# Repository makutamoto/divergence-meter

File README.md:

Divergence Meter
=====
PICの勉強のために作りました。
言語はMPASMです。

[実際に動いているところ（ブレッドボード上ですが）](https://twitter.com/makutamoto/status/1317350844782632962?s=20)

divergence_meter.X/
-----
MPLABのプロジェクトです。
PICのコードが入っています。

pcb/
-----
KICADのプロジェクトです。
基盤データが入っています。

scripts/
-----
ダイバージェンスメータに様々な情報を書き込むためのスクリプトを置いています。

### add.py
世界戦変動率を追加します。

### calibrate.py
現在時刻と同期します。

### clock.py
忘れた、不明。

### preview.py
世界戦変動率をプレビューします。

### remove.py
世界戦変動率を削除します。

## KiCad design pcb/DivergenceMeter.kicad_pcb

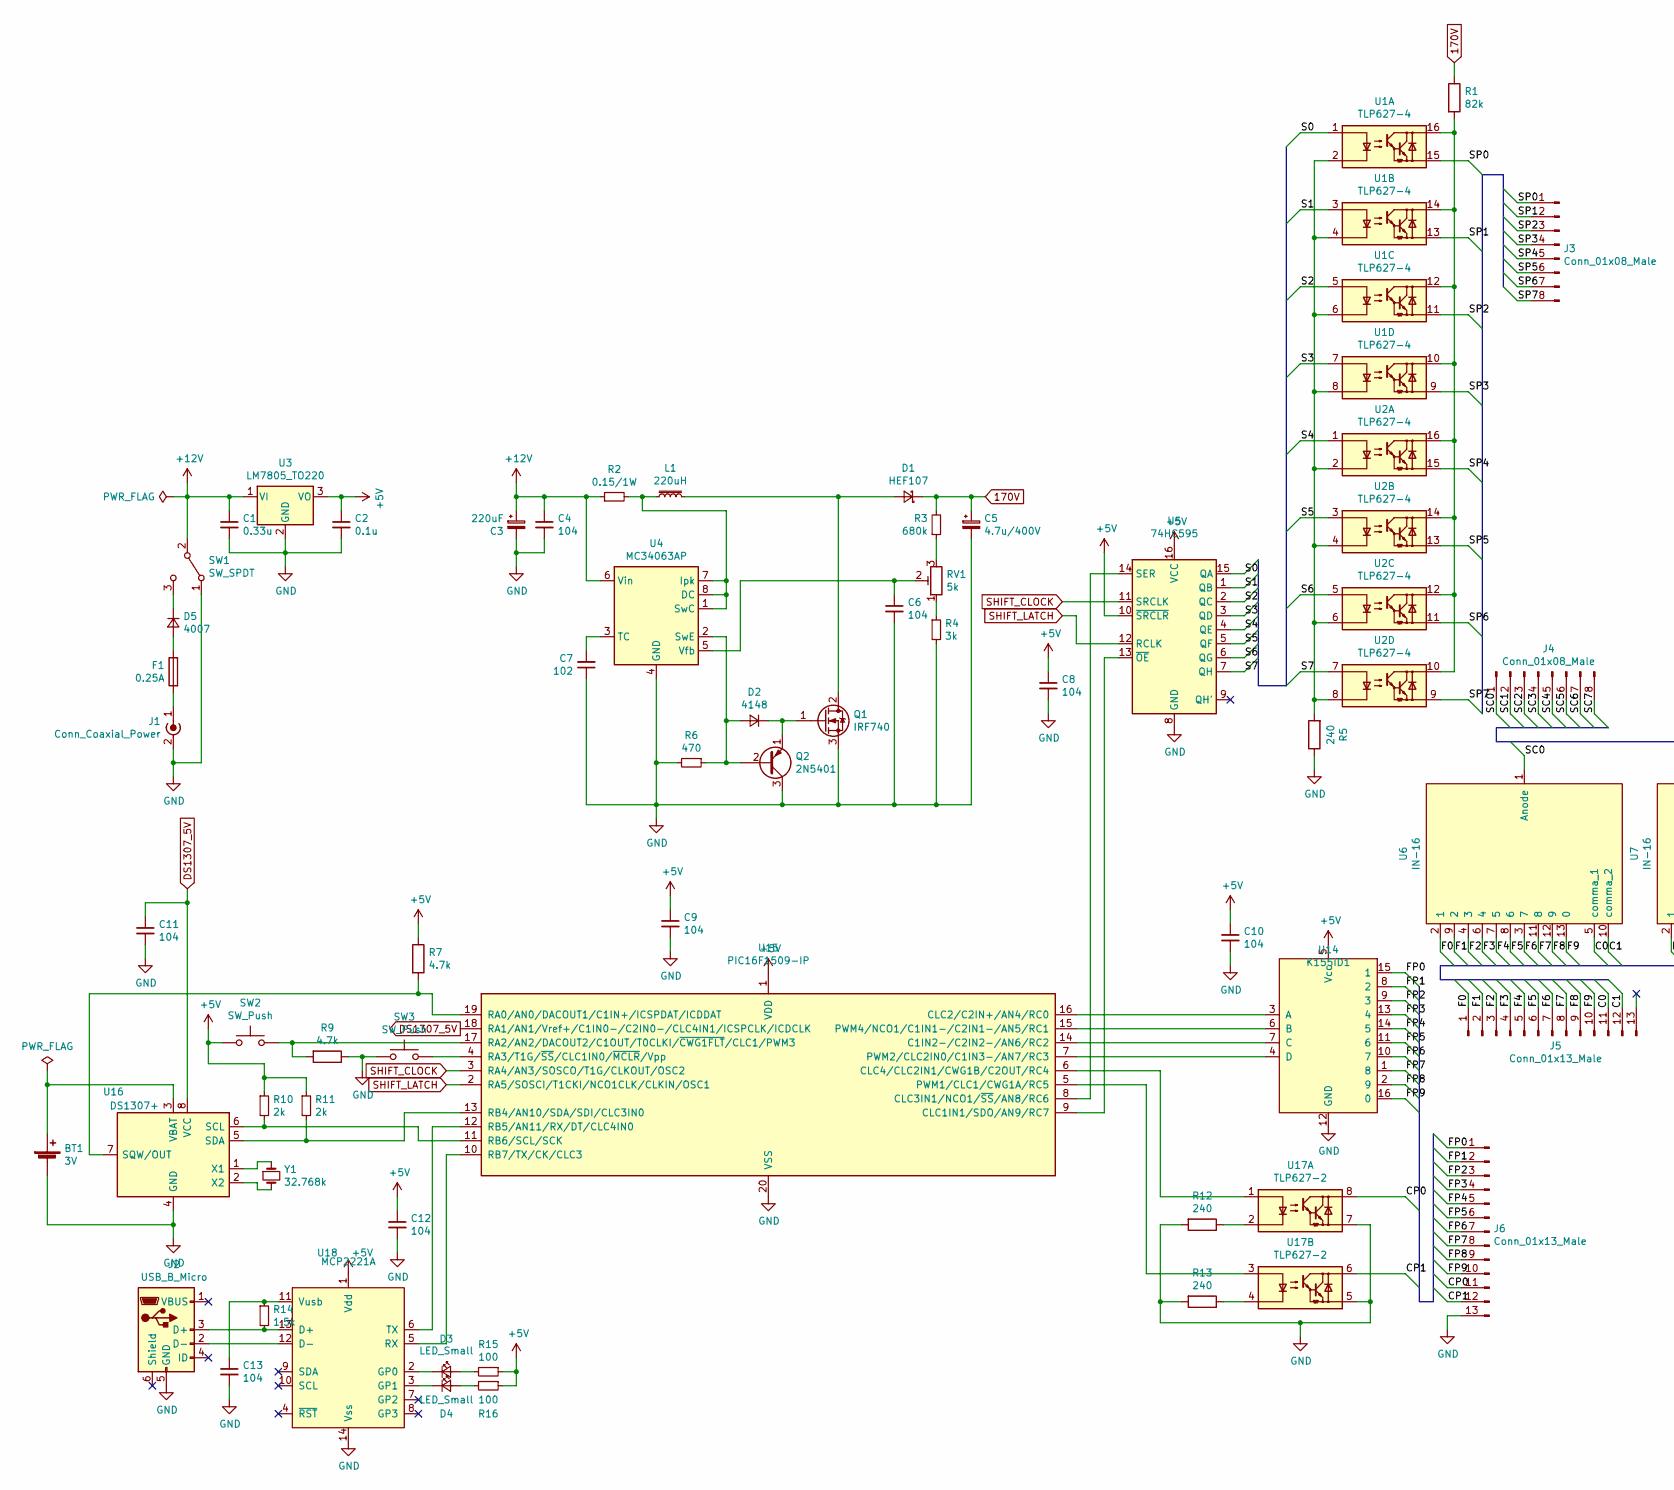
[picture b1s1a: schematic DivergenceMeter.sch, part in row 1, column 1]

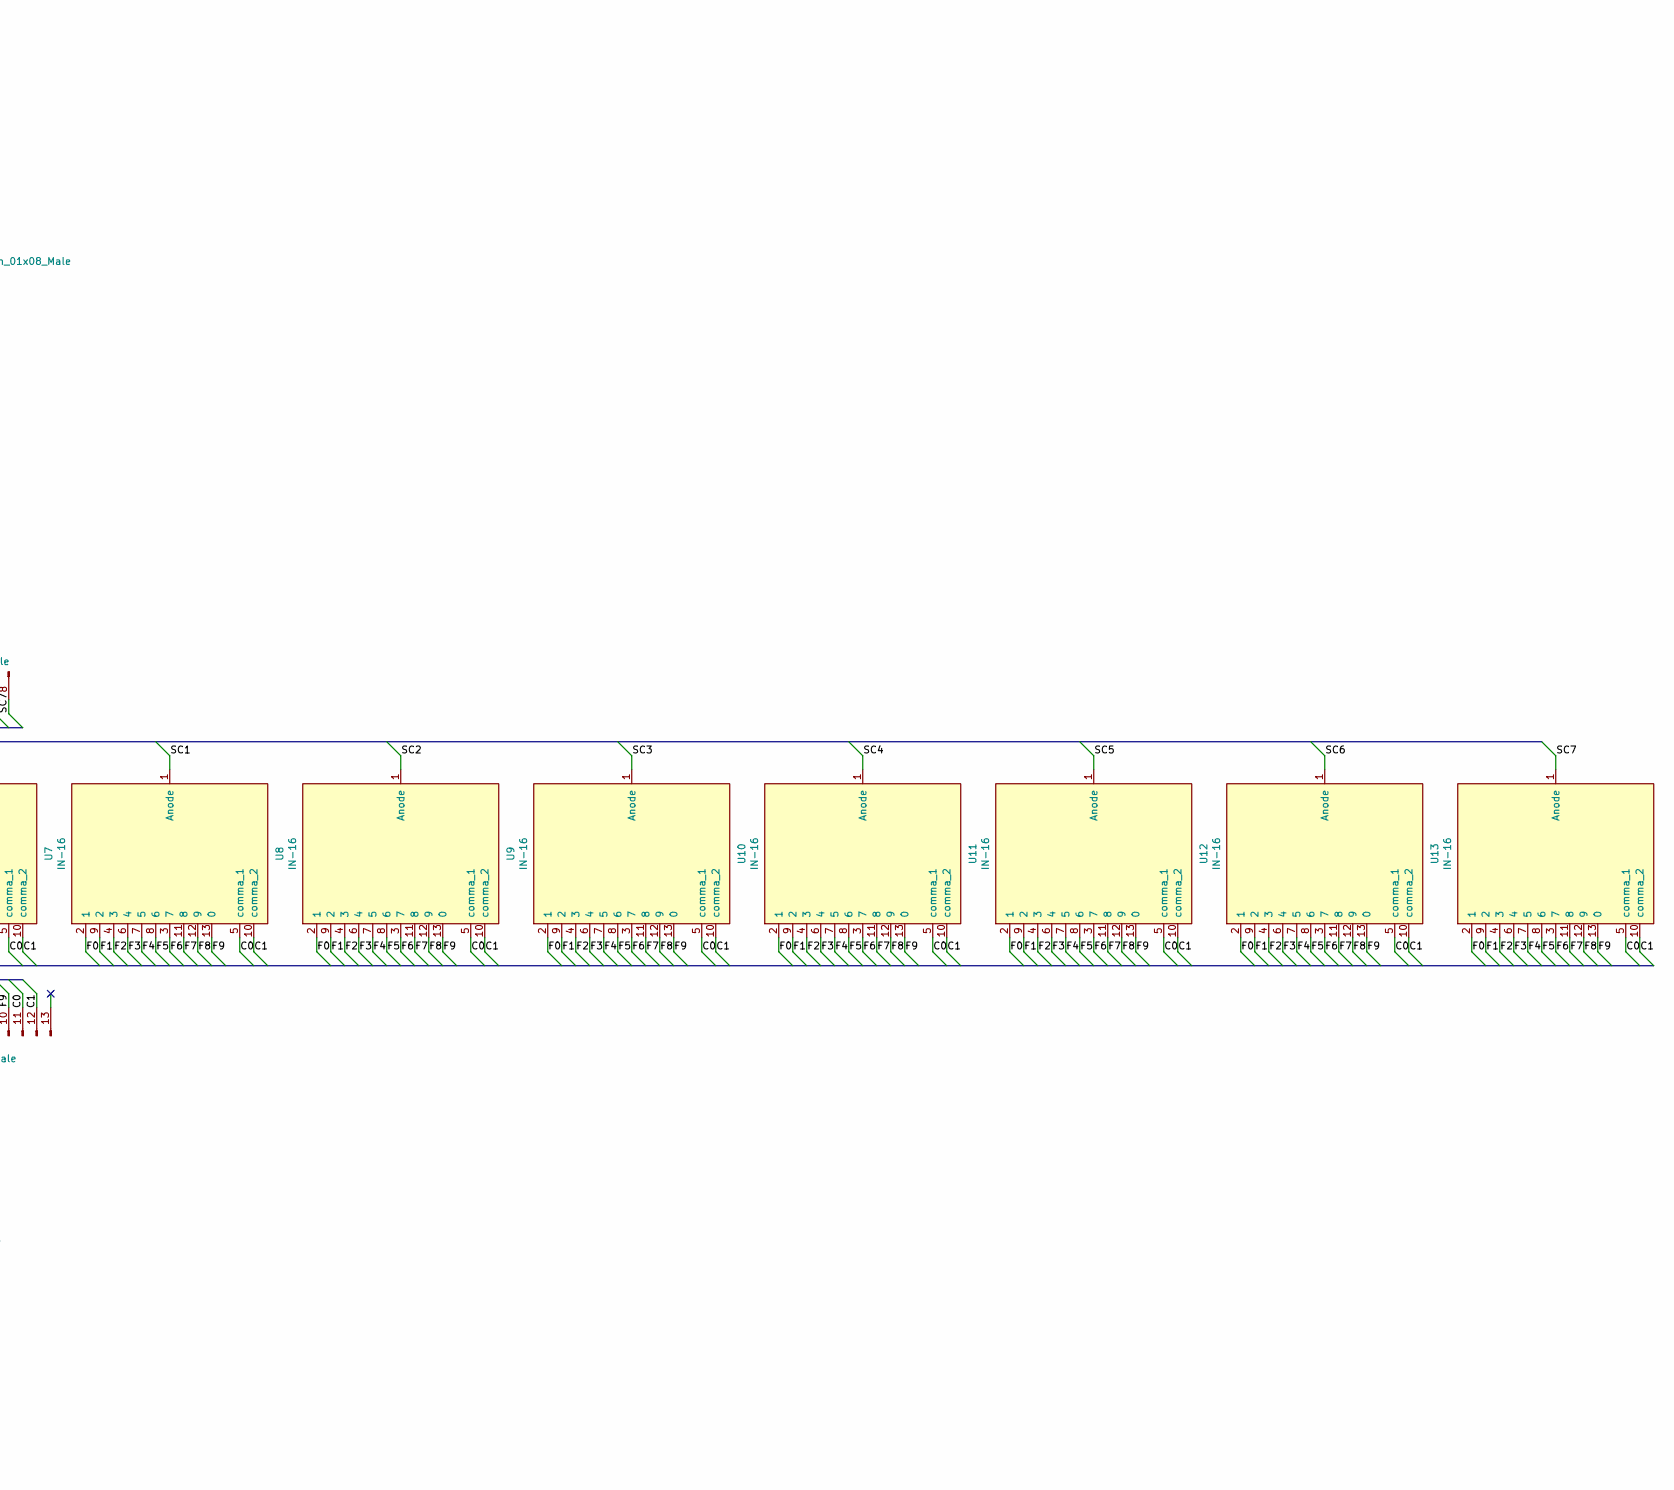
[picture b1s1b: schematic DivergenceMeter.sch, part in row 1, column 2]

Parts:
BT1: 3V; BatteryHolder_Keystone_103_1x20mm
C1: 0.33u; C_Radial_D10.0mm_H12.5mm_P5.00mm
C2: 0.1u; C_Radial_D10.0mm_H12.5mm_P5.00mm
C3: 220uF; CP_Radial_D10.0mm_P5.00mm
C4, C6, C8, C9, C10, C11, C12, C13: 104; C_Radial_D10.0mm_H12.5mm_P5.00mm
C5: 4.7u/400V; CP_Radial_D10.0mm_P5.00mm
C7: 102; C_Radial_D16.0mm_H25.0mm_P7.50mm
D1: HEF107; D_DO-41_SOD81_P10.16mm_Horizontal
D2: 4148; D_DO-35_SOD27_P7.62mm_Horizontal
D3, D4: LED_Small; LED_D3.0mm
D5: 4007; D_DO-41_SOD81_P10.16mm_Horizontal
F1: 0.25A; Fuseholder_Cylinder-5x20mm_Schurter_0031_8201_Horizontal_Op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
J1: Conn_Coaxial_Power; DC Jack
J2: USB_B_Micro; USB_Micro-B_Molex-105017-0001
J3, J4: Conn_01x08_Male; JST_XH_B08B-XH-A_1x08_P2.50mm_Vertical
J5, J6: Conn_01x13_Male; JST_XH_B13B-XH-A_1x13_P2.50mm_Vertical
L1: 220uH; L_Radial_D6.0mm_P4.00mm
Q1: IRF740; TO-220-3_Vertical
Q2: 2N5401; TO-92_Inline
R1: 82k; R_Axial_DIN0207_L6.3mm_D2.5mm_P10.16mm_Horizontal
R2: 0.15/1W; R_Axial_DIN0207_L6.3mm_D2.5mm_P10.16mm_Horizontal
R3: 680k; R_Axial_DIN0207_L6.3mm_D2.5mm_P10.16mm_Horizontal
R4: 3k; R_Axial_DIN0207_L6.3mm_D2.5mm_P10.16mm_Horizontal
R5, R12, R13: 240; R_Axial_DIN0207_L6.3mm_D2.5mm_P10.16mm_Horizontal
R6: 470; R_Axial_DIN0207_L6.3mm_D2.5mm_P10.16mm_Horizontal
R7, R9: 4.7k; R_Axial_DIN0207_L6.3mm_D2.5mm_P10.16mm_Horizontal
R10, R11: 2k; R_Axial_DIN0207_L6.3mm_D2.5mm_P10.16mm_Horizontal
R14: 1.5k; R_Axial_DIN0207_L6.3mm_D2.5mm_P10.16mm_Horizontal
R15, R16: 100; R_Axial_DIN0207_L6.3mm_D2.5mm_P10.16mm_Horizontal
RV1: 5k; Potentiometer_Bourns_3266P_Horizontal
SW1: SW_SPDT; Slide Switch
SW2, SW3: SW_Push; SW_PUSH_6mm_H5mm
U1, U2: TLP627-4; DIP-16_W7.62mm
U3: LM7805_TO220; TO-220-3_Vertical
U4: MC34063AP; DIP-8_W7.62mm
U5: 74HC595; DIP-16_W7.62mm
U6, U7, U8, U9, U10, U11, U12, U13: IN-16
U14: K155ID1; DIP-16_W7.62mm
U15: PIC16F1509-IP; DIP-20_W7.62mm_Socket
U16: DS1307+; DIP-8_W7.62mm
U17: TLP627-2; DIP-8_W7.62mm
U18: MCP2221A; DIP-14_W7.62mm
Y1: 32.768k; Crystal_DS26_D2.0mm_L6.0mm_Vertical

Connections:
170V: C5.1, D1.1 (K), R1.1, R3.2
+5V: C2.1, C8.1, C9.1, C10.1, C12.1, R7.1, R10.1, R11.1, R15.1, R16.1, SW2.1, U3.3 (VO), U5.10 (~SRCLR), U5.16 (VCC), U14.5 (Vcc), U15.1 (VDD), U18.1 (Vdd)
+12V: C1.1, C3.1, C4.1, R2.1, SW1.2 (B), U3.1 (VI), U4.6 (Vin)
/C0: J5.11, U6.5 (comma_1), U7.5 (comma_1), U8.5 (comma_1), U9.5 (comma_1), U10.5 (comma_1), U11.5 (comma_1), U12.5 (comma_1), U13.5 (comma_1)
/C1: J5.12, U6.10 (comma_2), U7.10 (comma_2), U8.10 (comma_2), U9.10 (comma_2), U10.10 (comma_2), U11.10 (comma_2), U12.10 (comma_2), U13.10 (comma_2)
/CP0: J6.11, U17.8
/CP1: J6.12, U17.6
/F0: J5.1, U6.2 (1), U7.2 (1), U8.2 (1), U9.2 (1), U10.2 (1), U11.2 (1), U12.2 (1), U13.2 (1)
/F1: J5.2, U6.9 (2), U7.9 (2), U8.9 (2), U9.9 (2), U10.9 (2), U11.9 (2), U12.9 (2), U13.9 (2)
/F2: J5.3, U6.4 (3), U7.4 (3), U8.4 (3), U9.4 (3), U10.4 (3), U11.4 (3), U12.4 (3), U13.4 (3)
/F3: J5.4, U6.6 (4), U7.6 (4), U8.6 (4), U9.6 (4), U10.6 (4), U11.6 (4), U12.6 (4), U13.6 (4)
/F4: J5.5, U6.7 (5), U7.7 (5), U8.7 (5), U9.7 (5), U10.7 (5), U11.7 (5), U12.7 (5), U13.7 (5)
/F5: J5.6, U6.8 (6), U7.8 (6), U8.8 (6), U9.8 (6), U10.8 (6), U11.8 (6), U12.8 (6), U13.8 (6)
/F6: J5.7, U6.3 (7), U7.3 (7), U8.3 (7), U9.3 (7), U10.3 (7), U11.3 (7), U12.3 (7), U13.3 (7)
/F7: J5.8, U6.11 (8), U7.11 (8), U8.11 (8), U9.11 (8), U10.11 (8), U11.11 (8), U12.11 (8), U13.11 (8)
/F8: J5.9, U6.12 (9), U7.12 (9), U8.12 (9), U9.12 (9), U10.12 (9), U11.12 (9), U12.12 (9), U13.12 (9)
/F9: J5.10, U6.13 (0), U7.13 (0), U8.13 (0), U9.13 (0), U10.13 (0), U11.13 (0), U12.13 (0), U13.13 (0)
/FP0: J6.1, U14.15 (1)
/FP1: J6.2, U14.8 (2)
/FP2: J6.3, U14.9 (3)
/FP3: J6.4, U14.13 (4)
/FP4: J6.5, U14.14 (5)
/FP5: J6.6, U14.11 (6)
/FP6: J6.7, U14.10 (7)
/FP7: J6.8, U14.1 (8)
/FP8: J6.9, U14.2 (9)
/FP9: J6.10, U14.16 (0)
/S0: U1.1, U5.15 (QA)
/S1: U1.3, U5.1 (QB)
/S2: U1.5, U5.2 (QC)
/S3: U1.7, U5.3 (QD)
/S4: U2.1, U5.4 (QE)
/S5: U2.3, U5.5 (QF)
/S6: U2.5, U5.6 (QG)
/S7: U2.7, U5.7 (QH)
/SC0: J4.1, U6.1 (Anode)
/SC1: J4.2, U7.1 (Anode)
/SC2: J4.3, U8.1 (Anode)
/SC3: J4.4, U9.1 (Anode)
/SC4: J4.5, U10.1 (Anode)
/SC5: J4.6, U11.1 (Anode)
/SC6: J4.7, U12.1 (Anode)
/SC7: J4.8, U13.1 (Anode)
/SP0: J3.1, U1.15
/SP1: J3.2, U1.13
/SP2: J3.3, U1.11
/SP3: J3.4, U1.9
/SP4: J3.5, U2.15
/SP5: J3.6, U2.13
/SP6: J3.7, U2.11
/SP7: J3.8, U2.9
DS1307_5V: C11.1, U15.18 (RA1/AN1/Vref+/C1IN0-/C2IN0-/CLC4IN1/ICS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), U16.8 (VCC)
GND: BT1.2 (-), C1.2, C2.2, C3.2, C4.2, C5.2, C6.2, C7.1, C8.2, C9.2, C10.2, C11.2, C12.2, C13.2, J1.2 (Ext), J2.5 (GND), J6.13, Q1.3 (S), Q2.3 (C), R4.2, R5.1, R6.2, R9.1, R12.2, R13.2, SW1.1 (A), SW3.1, U3.2 (GND), U4.4 (GND), U5.8 (GND), U14.12 (GND), U15.20 (VSS), U16.4 (GND), U17.5, U17.7, U18.14 (Vss)
unnamed: BT1.1 (+), U16.3 (VBAT)
unnamed: C6.1, RV1.2, U4.5 (Vfb)
unnamed: C7.2, U4.3 (TC)
unnamed: C13.1, R14.1, U18.11 (Vusb)
unnamed: D1.2 (A), L1.2, Q1.2 (D)
unnamed: D2.1 (K), Q1.1 (G), Q2.1 (E)
unnamed: D2.2 (A), Q2.2 (B), R6.1, U4.2 (SwE)
unnamed: D3.1 (K), U18.2 (GP0)
unnamed: D3.2 (A), R15.2
unnamed: D4.1 (K), U18.3 (GP1)
unnamed: D4.2 (A), R16.2
unnamed: D5.1 (K), SW1.3 (C)
unnamed: D5.2 (A), F1.1
unnamed: F1.2, J1.1 (In)
unnamed: J2.2 (D-), U18.12 (D-)
unnamed: J2.3 (D+), R14.2, U18.13 (D+)
unnamed: L1.1, R2.2, U4.1 (SwC), U4.7 (Ipk), U4.8 (DC)
unnamed: R1.2, U1.10, U1.12, U1.14, U1.16, U2.10, U2.12, U2.14, U2.16
unnamed: R3.1, RV1.3
unnamed: R4.1, RV1.1
unnamed: R5.2, U1.2, U1.4, U1.6, U1.8, U2.2, U2.4, U2.6, U2.8
unnamed: R7.2, U15.19 (RA0/AN0/DACOUT1/C1IN+/ICSPDAT/ICDDAT), U16.7 (SQW/OUT)
unnamed: R9.2, SW2.2, U15.17 (RA2/AN2/DACOUT2/C1OUT/T0CLKI/~CWG1FLT~/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)
unnamed: R10.2, U15.11 (RB6/SCL/SCK), U16.6 (SCL)
unnamed: R11.2, U15.13 (RB4/AN10/SDA/SDI/CLC3IN0), U16.5 (SDA)
unnamed: R12.1, U17.2
unnamed: R13.1, U17.4
unnamed: SW3.2, U15.4 (RA3/T1G/~SS~/CLC1IN0/~MCLR~/Vpp)
unnamed: U14.3 (A), U15.16 (CLC2/C2IN+/AN4/RC0)
unnamed: U14.4 (D), U15.7 (PWM2/CLC2IN0/C1IN3-/AN7/RC3)
unnamed: U14.6 (B), U15.15 (PWM4/NCO1/C1IN1-/C2IN1-/AN5/RC1)
unnamed: U14.7 (C), U15.14 (C1IN2-/C2IN2-/AN6/RC2)
unnamed: U15.5 (PWM1/CLC1/CWG1A/RC5), U17.3
unnamed: U15.6 (CLC4/CLC2IN1/CWG1B/C2OUT/RC4), U17.1
unnamed: U5.14 (SER), U15.8 (CLC3IN1/NCO1/~SS~/AN8/RC6)
unnamed: U5.13 (~OE), U15.9 (CLC1IN1/SDO/AN9/RC7)
unnamed: U15.10 (RB7/TX/CK/CLC3), U18.5 (RX)
unnamed: U15.12 (RB5/AN11/RX/DT/CLC4IN0), U18.6 (TX)
unnamed: U16.1 (X1), Y1.1
unnamed: U16.2 (X2), Y1.2
SHIFT_CLOCK: U5.11 (SRCLK), U15.3 (RA4/AN3/SOSCO/T1G/CLKOUT/OSC2)
SHIFT_LATCH: U5.12 (RCLK), U15.2 (RA5/SOSCI/T1CKI/NCO1CLK/CLKIN/OSC1)

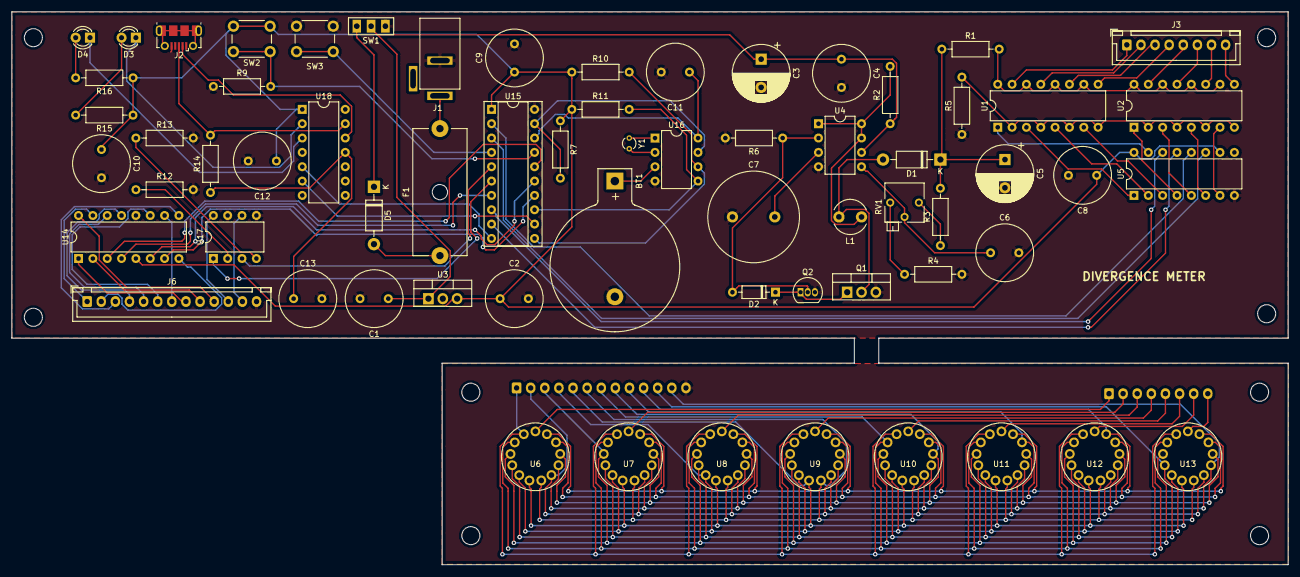
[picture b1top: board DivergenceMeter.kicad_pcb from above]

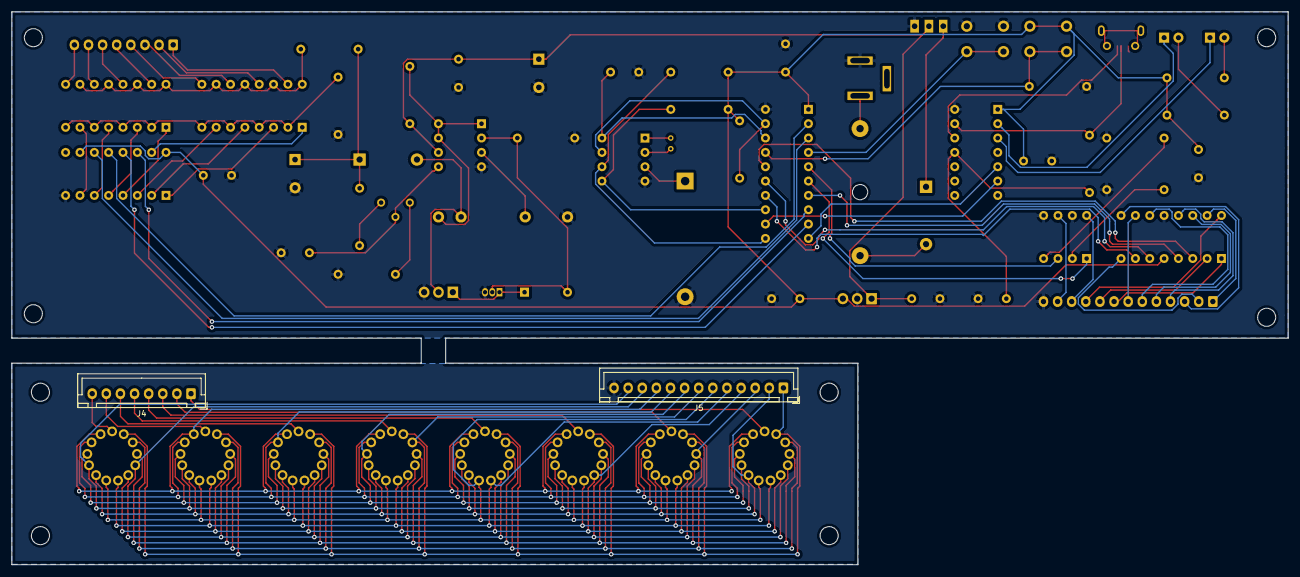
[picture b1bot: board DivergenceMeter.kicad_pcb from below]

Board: 2 copper layers, 226.1 x 97.9 mm, 67 parts (2 on the bottom side), 95 nets.

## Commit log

2020-10-17 + Initial Commit.
2020-10-17 + pcb
2020-10-17 + descriptions
2020-10-17 + video
